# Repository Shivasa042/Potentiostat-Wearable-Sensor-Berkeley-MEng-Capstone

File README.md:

# Wearable Potentiostat — EIS Sweat Sensor (Berkeley MEng Capstone)

Portable Electrochemical Impedance Spectroscopy (EIS) system for real-time sweat analysis. Built around an **ESP32-S3** MCU and **Analog Devices AD5940/AD5941** analog front-end (AFE). Two electrodes on a watch back-plate contact skin; the system sweeps **1 Hz – 200 kHz** and reports complex impedance over **USB serial**, **BLE**, and **SD card**.

---

## Contents

1. [Hardware](#hardware)
2. [Repository structure](#repository-structure)
3. [Getting started](#getting-started)
4. [Usage](#usage) — serial commands, **Command Prompt / PowerShell**, Python scripts, scenarios
5. [Frequency range and sweep duration](#frequency-range-and-sweep-duration)
6. [How EIS works on this board](#how-eis-works-on-this-board)
7. [Errors, fixes, and known issues](#errors-fixes-and-known-issues)
8. [Firmware features](#firmware-features)
9. [Companion apps](#companion-apps) — **PHEW web app**, iOS, Android; BLE setup and usage
10. [Pin configuration](#pin-configuration)
11. [License](#license)

---

## Hardware

| Component | Details |
|-----------|---------|
| **MCU** | ESP32-S3 (240 MHz, Wi-Fi + BLE 5.0) |
| **AFE** | AD5940 / AD5941 — waveform generator, DFT engine, programmable-gain TIA |
| **Electrodes** | 2-electrode (CE0 + SE0), mounted on Apple Watch back-plate for sweat contact |
| **SPI bus** | Shared: AFE, SD card, and (Akshay PCB) ST7789 display — each device has its own CS |
| **Storage** | MicroSD card slot (FAT32, SPI) |
| **Wireless** | BLE — web companion, iOS app, or legacy Android |
| **Power** | USB-C or 3.7 V LiPo |
| **RCAL** | On-board calibration resistor, default **10 kΩ** — used internally by the AFE for ratiometric impedance calculation (not the load) |

### Two board variants

| | HELPStat V2 (bench/dev) | New_EIS_PCB_Akshay (final wearable) |
|---|---|---|
| AFE CS | GPIO 38 (or 11 on Eagle V2) | GPIO 38 |
| AFE interrupt | Hardware (GPIO 9) | None — SPI DFT polling |
| SD CS | GPIO 21 | GPIO 40 |
| Button | GPIO 7 | GPIO 13 |
| LED | GPIO 6 | None (use display) |
| Display | None | ST7789 240×280 SPI (ER-TFT1.69-4) — see [Pin configuration](#pin-configuration) |
| PSRAM | No | **Firmware uses internal RAM only** (`BOARD_HAS_PSRAM=0` in `eis-pcb-akshay`; avoids boot/USB instability when PSRAM does not init) |
| PlatformIO env | `lab-board-cs38` | `eis-pcb-akshay` |

KiCad 9 design files for the final PCB are in `boards/New_EIS_PCB_Akshay/`.

---

## Repository structure

```
src/main.cpp                   Firmware entry point, serial commands, measurement loop
src/eis_board_ui.cpp           SPI display driver for New_EIS_PCB_Akshay
lib/HELPStatLib/               Core library (AD5940 driver, EIS sweep, BLE, SD, LMA fit)
  HELPStat.cpp/h               High-level sweep, BLE transmit, SD save
  ad5940.c/h                   Low-level AD5940 register driver
  ad594x.cpp                   MCU-side SPI, interrupt/poll, resource init
  Impedance.c/h                Impedance math helpers
  lma.cpp/h                    Levenberg-Marquardt curve fitting (Rct, Rs)
  constants.h                  Pin definitions, board-specific macros
  eis_board_ui.h               Display UI header (C-linkage)
lib/Eigen/                     Eigen math library (used by LMA)
boards/custom_s3.json          PlatformIO board definition
boards/New_EIS_PCB_Akshay/     KiCad project (schematic + 4-layer PCB)
docs/                          Technical docs (features, modes, improvements)
testing/                       Python scripts for serial capture, plotting
web/helpstat-app/              PHEW web companion app (Chrome/Edge, Web Bluetooth)
ios/HELPStatCompanion/         Native iOS BLE companion (SwiftUI)
Originallibraries/             Legacy HELPStat reference (Android app, original firmware, Eagle PCB)
platformio.ini                 Build configuration
```

---

## Getting started

### Prerequisites

- **VS Code + PlatformIO** extension (builds the firmware)
- **Python 3.8+** with `pip install -r requirements.txt` (for testing scripts)
- **USB-C cable** to the board

### Build and flash

1. Open this folder in VS Code. PlatformIO auto-detects `platformio.ini`.
2. Connect the board via USB-C.
3. Build and upload (from project root):

```bash
# HELPStat V2 / bench board (CS=38, SPI DFT polling — no AFE IRQ required):
python -m platformio run -e lab-board-cs38 -t upload --upload-port COM3

# New EIS PCB (Akshay) — display + SD CS=40:
python -m platformio run -e eis-pcb-akshay -t upload --upload-port COM3
```

Replace `COM3` with your actual port. Close any serial monitor before uploading.

4. Open a serial monitor at **115200 baud**.

> **Windows:** After the first flash, you may need to unplug and re-plug USB once so the ESP32-S3 exits the ROM bootloader.

---

## Usage

All serial traffic is **115200 baud**, commands end with a **newline** (`\n` or `\r\n`).

### Command summary

| Command | Description |
|---------|-------------|
| `HELP` | List all commands |
| `STATUS` | Show wearable timer state and last sweep time |
| `SHOW` | Print current measurement parameters |
| `CHECK` | Read AD5940 chip ID (SPI connectivity test) |
| `MEASURE` | Run sweep with current parameters |
| `MEASURE:SAMPLE` | Default sweep: 200 kHz → 1 Hz, 10 pts/decade, 200 mV |
| `MEASURE:<14 params>` | Custom sweep (see below) |
| `SET:<14 params>` | Set parameters without measuring |
| `WEARABLE:ON` / `OFF` | Enable/disable automatic timed sweeps |
| `INTERVAL:N` | Auto-sweep interval in seconds (min 10, default 300) |
| `STOP` | Abort a running sweep immediately (also works mid-sweep) |
| `RCAL:ohms` | Set RCAL value and save to NVS (e.g. `RCAL:10000`) |
| `RCAL:SHOW` | Print stored and runtime RCAL values |
| `DISPLAYRANGE:min,max,val[,title]` | Update SPI display (Akshay PCB only) |

### 14-parameter `MEASURE` format

```
MEASURE:mode,startFreq,endFreq,numPoints,biasVolt,zeroVolt,rcalVal,extGain,dacGain,rct_est,rs_est,numCycles,delaySecs,amplitude
```

| # | Parameter | Example | Notes |
|---|-----------|---------|-------|
| 1 | mode | 0 | 0=EIS, 1=CV, 2=IT, 3=CP, 4=DPV, 5=SWV, 6=OCP |
| 2 | startFreq | 200000 | Hz (often the high end of the sweep) |
| 3 | endFreq | 1 | Hz (often the low end) |
| 4 | numPoints | 10 | Points per decade (log sweep) |
| 5 | biasVolt | 0.0 | DC bias (V) |
| 6 | zeroVolt | 0.0 | Zero voltage (V) |
| 7 | rcalVal | 10000 | Calibration resistor (Ohms) — match your board's RCAL |
| 8 | extGain | 1 | Excitation buffer gain (1=x2) |
| 9 | dacGain | 1 | DAC gain (1=x1) |
| 10 | rct_est | 127000 | Estimated Rct (Ohms) — seed for LMA fit |
| 11 | rs_est | 150 | Estimated Rs (Ohms) — seed for LMA fit |
| 12 | numCycles | 0 | Repeat cycles |
| 13 | delaySecs | 0 | Delay between cycles (s) |
| 14 | amplitude | 200 | AC excitation (mV, 0-800) |

**Example — full-span sweep (200 kHz → 1 Hz, 5 pts/decade, 10 kΩ RCAL, 150 mV):**

```
MEASURE:0,200000,1,5,0.0,0.0,10000.0,1,1,127000.0,150.0,0,0,150
```

### Running an EIS sweep from Command Prompt or PowerShell (Windows)

Windows does not include a serial terminal in `cmd.exe`. Use **Python + pyserial** (same as the repo's test scripts).

1. **Install once:**

```bash
pip install pyserial
```

2. **Close anything else using the COM port** (VS Code Serial Monitor, another Python script, etc.).

3. **Send a command and print the response** — adjust `COM3` and timeouts as needed. Long sweeps can take **many minutes**; increase the inner `while` time limit if needed.

**Default firmware sample sweep (`MEASURE:SAMPLE`):**

```powershell
python -c "import serial,time; s=serial.Serial('COM3',115200,timeout=600); s.write(b'MEASURE:SAMPLE\r\n'); t=time.time();
while time.time()-t<900:
    line=s.readline()
    if line: print(line.decode(errors='replace').rstrip())"
```

**Custom 14-parameter sweep** (same example as the table above):

```powershell
python -c "import serial,time; s=serial.Serial('COM3',115200,timeout=600); s.write(b'MEASURE:0,200000,1,5,0.0,0.0,10000.0,1,1,127000.0,150.0,0,0,150\r\n'); t=time.time();
while time.time()-t<900:
    line=s.readline()
    if line: print(line.decode(errors='replace').rstrip())"
```

4. **Interactive alternative** — type commands by hand:

```bash
python -m platformio device monitor -p COM3 -b 115200
```

Then type `MEASURE:SAMPLE` or a full `MEASURE:0,...` line and press Enter.

### Python scripts in `testing/`

```bash
# Default 2-point sweep (10 kHz → 1 kHz):
python testing/scenario1_serial_sample.py COM3

# Single frequency at 10 kHz:
python testing/scenario1_serial_sample.py COM3 10000
```

### Three usage scenarios

1. **Laptop + USB (development)** — Flash, open serial (or Command Prompt as above), send `MEASURE:SAMPLE`, read CSV from the terminal or a script.
2. **Standalone (button + SD)** — Press button on GPIO 7 (bench) or GPIO 13 (Akshay). Results save to SD at `/eis/sweep_1Hz_200kHz.csv` (path/name set in firmware).
3. **Wearable (BLE, battery)** — Send `WEARABLE:ON` once. Board auto-sweeps at the configured interval. Data via BLE (web/iOS) and SD card.

---

## Frequency range and sweep duration

- **Practical sweep span in this firmware:** about **1 Hz – 200 kHz** (high end is what the code and gain schedule target; AD5941 family supports a similar band depending on clock and configuration).
- **Number of frequency points** (log sweep, `startFreq > endFreq`):

  `SweepPoints = (1.5 + (log10(startFreq) - log10(endFreq)) x numPoints) - 1`

  Example: 200 kHz → 1 Hz at **5 points/decade** = **27 points**; at **10 points/decade** = **54 points**.

- **Time per point** depends on frequency (settling + DFT). **Low Hz is slow** (several seconds per point is normal).

### Measured sweep timings (10 kOhm load resistor)

| Sweep | Points | Approx. duration | Notes |
|-------|--------|-------------------|-------|
| Single-point 200 kHz | 1 | ~2 s | Fastest; use small span trick (see below) |
| Single-point 200 Hz | 1 | ~3 s | |
| 200 kHz → 10 Hz, 5 pts/decade | 22 | ~30 s | Good for quick characterization |
| 200 kHz → 1 Hz, 5 pts/decade | 27 | **~108 s** | Full wearable range (`MEASURE:SAMPLE` default) |
| 200 kHz → 1 Hz, 10 pts/decade | 54 | ~4-6 min | High-resolution; pass `numPoints=10` in custom `MEASURE:` |

Low-frequency points (< 10 Hz) are dominated by DFT collection time inside the AD5940 — this is a hardware constraint. The 1 Hz point alone takes several seconds.

### Sweep speed tuning (firmware defaults)

The firmware balances speed and accuracy through these parameters:

| Parameter | Value | Location | Effect |
|-----------|-------|----------|--------|
| Settling periods | 2 cycles | `HELPStat.cpp settlingDelay()` | Fewer AC cycles before DFT capture |
| Averages per point | 1 | `HELPStat.h _numAverages` | Single validated measurement per frequency |
| Gain-switch delay | 50 ms | `HELPStat.cpp` / `runSweep()` | Reduced from 200 ms; stable with resistive loads |
| Default pts/decade | 5 | `main.cpp MEASURE:SAMPLE` | 27 points for full 1 Hz–200 kHz span |

These can be increased for noisier electrochemical loads (e.g., set `_numAverages = 3` for sweat sensors). The custom `MEASURE:` command accepts any `numPoints` value.

### Sample measurement results (10 kOhm load resistor across CE0-SE0)

| Test | Magnitude | Phase | Rct (fit) | Rs (fit) |
|------|-----------|-------|-----------|----------|
| 200 kHz single | ~335 Ohm | ~2.6 deg | — | — |
| 200 Hz single | ~332 Ohm | ~0.05 deg | — | — |
| 200 kHz → 10 Hz (22 pts) | 311-357 Ohm | -4 to +4 deg | 32.3 Ohm | 323.4 Ohm |
| 200 kHz → 1 Hz (27 pts) | 303-365 Ohm | -3.4 to +4.5 deg | -29.5 Ohm | 325.5 Ohm |

These values are from a bench test with a nominal 10 kOhm resistor (actual ~327 Ohm measured — the parallel combination of the 10 kOhm load with the AFE's internal RTIA/feedback path produces the observed lower magnitude).

### Single-frequency caveat

If **`startFreq` equals `endFreq`**, the sweep math yields **zero points** and the measurement hangs. For an effectively single frequency, use a **tiny span**, e.g. `200000` → `199000` with `numPoints=1`.

### Stopping a sweep mid-flight

You can abort a running sweep at any time. The firmware checks for abort requests between each frequency point.

| Method | How | Where |
|--------|-----|-------|
| **PHEW web app** | Click the red **Stop** button (replaces "Run sweep" during a sweep) | `web/helpstat-app/` |
| **Serial** | Send `STOP` (case-insensitive) over the serial connection | Any serial terminal, pyserial script |
| **BLE programmatic** | Write byte `2` to the `start` characteristic | Any BLE client using the GATT UUIDs |

On abort the firmware shuts down the AFE cleanly, prints any partial CSV data collected so far, and skips the Rct/Rs curve fit and BLE data transmission (partial data would produce unreliable fits). The board is immediately ready for the next command.

### Long sweeps + USB

On some PCs the ESP32-S3 **USB Serial/JTAG** link can **glitch or disconnect** during long runs. The firmware still **writes results to the SD card** when a card is present — check `/eis/` on the card if the serial stream stops early.

---

## How EIS works on this board

1. AD5940 waveform generator outputs a sine wave at the target frequency through **CE0** (counter electrode).
2. Current flows through the **load** (sweat between the two electrodes) and returns through **SE0** (sense electrode).
3. The **HSTIA** (transimpedance amplifier) converts the current to voltage. Gain resistor is auto-selected per frequency band.
4. The on-chip **DFT engine** extracts real and imaginary components.
5. Impedance is computed ratiometrically against **RCAL** (the known calibration resistor on the board).
6. The firmware sweeps all frequencies, outputting CSV with columns: `Frequency(Hz), Real(Ohm), Imaginary(Ohm), Magnitude(Ohm), Phase(Degrees)`.
7. A Levenberg-Marquardt fit estimates **Rct** (charge transfer resistance) and **Rs** (solution resistance).

### RCAL vs load — what each does

- **RCAL** (on-board, 10 kΩ default): An internal **reference** resistor. The AFE measures it at each frequency to calibrate its gain path. It is **not** the unknown under test. You do not wire CE0/SE0 to RCAL for normal EIS.
- **Load** (between CE0 and SE0): The **unknown impedance** you are measuring. For bench testing this is often a known resistor. For the wearable, this is **sweat/skin** between the watch electrodes.

If there is **no conductive path** between CE0 and SE0 (open circuit, dry skin, electrodes not touching), the DFT engine gets no valid signal and times out — producing `NaN` results.

---

## Errors, fixes, and known issues

### DFT poll timeout → NaN results

**Symptom:** `ERROR: DFT poll timeout (~30 s)` and CSV values are `nan`.

| Cause | Fix |
|-------|-----|
| **No load between CE0 and SE0** | Bench: place a **known resistor** across CE0-SE0. Wearable: moist contact / sweat path. |
| **Dry skin / no sweat** | Electrodes need a conductive medium; saline drop for testing if needed. |
| **Wrong AFE CS pin** | Match `CS` in `constants.h` to your PCB (38 for Akshay / this bench setup; 11 for HELPStat V2 Eagle). |
| **Missing interrupt wire** (HELPStat V2 only) | AFE GPIO0 → MCU GPIO9. Akshay PCB uses **SPI polling** instead (`AFE_USE_HARDWARE_IRQ_GPIO=0` in `lab-board-cs38` / Akshay path). |

### PSRAM / boot loop / USB drops right after boot (Akshay env)

**Symptom:** ROM prints `PSRAM ID read error` or serial **disconnects** mid-banner; `ClearCommError` / port errors in Python.

**Fix:** Build **`eis-pcb-akshay`** with **PSRAM disabled** in `platformio.ini` (`board_build.psram_type = disabled`, `-DBOARD_HAS_PSRAM=0`). The chip may report embedded PSRAM in esptool while the ROM/app init still fails; **internal RAM** is enough for this firmware.

### Display not showing anything (Akshay PCB — ST7789)

**Symptom:** Firmware prints `eis_board_ui: display ready (ST7789)` but the screen is dark.

| Cause | Fix |
|-------|-----|
| **Backlight not enabled** | GPIO 14 (ESP.PWM) drives Q3 N-FET gate to sink LED cathode. Firmware now drives GPIO 14 HIGH after display init. |
| **FPC cable not seated** | The 18-pin 0.5 mm FPC connector (J13) has a flip-top ZIF latch. Ensure the cable is fully inserted and the latch is **closed**. |
| **SPI bus contention** | Firmware deselects AD5941 (GPIO 38 HIGH) before display transactions. If issues persist, check solder joints on J13. |

**Display backlight circuit (from KiCad):**

```
+3V3 → R (0402 current limiter) → J13 pin 3 (LED anode)
J13 pin 2 (LED cathode, /K) → Q3 drain (IRLML6344 N-FET)
Q3 source → GND
Q3 gate ← GPIO 14 (ESP.PWM)
```

The display is a **ER-TFT1.69-4** (BuyDisplay), 1.69" 240x280 IPS TFT, ST7789V controller, 4-wire SPI. Datasheet: [ER-TFT1.69-4](https://www.buydisplay.com/download/manual/ER-TFT1.69-4_Datasheet.pdf), [ST7789V IC](https://www.buydisplay.com/download/ic/ST7789.pdf).

On boot, the firmware runs a diagnostic sequence: **3 backlight blinks** (GPIO 14 toggle), then fills **RED → GREEN → BLUE** (600 ms each), then displays **HELLO WORLD** in white text. If no blinks are visible, the issue is hardware (FPC cable, backlight circuit, or display module).

### COM port issues (Windows)

| Symptom | Fix |
|---------|-----|
| `PermissionError` / port busy | Another program holds the port. Close Serial Monitor and kill stuck Python processes. |
| Port disappears after flash | Unplug and re-plug USB once (common on ESP32-S3). |
| Upload fails | Close serial monitor before uploading. |

### Build errors

| Error | Fix |
|-------|-----|
| `pio not recognized` | Use `python -m platformio run ...` |
| `#define CS` clash with Adafruit | Do not include `constants.h` before Adafruit headers in display code — already handled in `eis_board_ui.cpp`. |
| `-DMOSI` / `-DMISO` / `-DSCK` build flags | Do **not** pass these on Arduino-ESP32 3.x — they clash with `pins_arduino.h`. Edit `constants.h` instead. |

### EIS data quality

| Issue | Explanation |
|-------|-------------|
| `inf` magnitude | Open circuit or loose electrode connection. |
| Jumps at certain frequencies | RTIA gain switching; hysteresis helps but extreme mismatches can still show artifacts. |
| Fit Rct/Rs stuck at defaults | Poor data; fix wiring and **RCAL** first, then tune `rct_est` / `rs_est`. |
| Slow sweep at low frequencies | Normal — more cycles at low Hz. |

---

## Firmware features

- **Data validation**: Bad DFT measurements (NaN, inf, out-of-range) are detected and retried (up to 4x) or recorded as NaN.
- **DFT poll timeout**: ~30 s timeout prevents infinite hangs on open circuit or stuck interrupt path.
- **Gain hysteresis**: 10% frequency margin on RTIA switching reduces oscillation at band boundaries.
- **Averaging**: Configurable per-point averaging (`_numAverages`, default 1; increase for noisy electrochemical loads).
- **Speed-optimized defaults**: Settling delay (2 AC periods), 50 ms gain-switch delays, 5 pts/decade — full 1 Hz–200 kHz sweep in ~108 s.
- **Sweep abort**: `STOP` serial command or BLE `start=2` write aborts a running sweep between frequency points. AFE shuts down cleanly; partial data is printed.
- **SPI DFT polling**: On PCBs without AFE→MCU interrupt (Akshay), DFTRDY is polled over SPI.
- **RCAL in NVS**: `RCAL:` stores calibration value in flash (survives reboot).
- **Wearable auto-sweep**: Timer-based sweeps for field use (`WEARABLE:ON`, `INTERVAL:N`).
- **Display UI** (Akshay): Live sweep progress on ST7789; `DISPLAYRANGE` serial command for custom display.
- **Display backlight** (Akshay): GPIO 14 PWM drives Q3 N-FET for backlight control; blink test on boot.
- **Temperature logging**: AD5940 die temperature readout (approximate).

See `docs/NEW_FEATURES.md` for more detail.

---

## Companion apps

**GitHub only stores source code.** Nothing is automatically "built" or hosted for you. You run each app locally (or deploy the web app to your own hosting). The firmware must be on the board and **BLE enabled** in the sketch for phone/browser connections to work.

| Platform | Location | Notes |
|----------|----------|-------|
| **PHEW Web App** (Chrome/Edge) | `web/helpstat-app/` | Static site + Web Bluetooth. Needs **HTTPS or localhost**. |
| **iOS** (native) | `ios/HELPStatCompanion/` | Open in **Xcode**, build to a **physical iPhone** (recommended) or Simulator (BLE is limited). |
| **Android** (legacy) | `Originallibraries/HELPStat-main 4/HELPStat/Software/App/` | Open in **Android Studio**, Gradle build. Not actively maintained. |

### Bluetooth: advertised name, pairing, and which devices can connect

- **Name you should see when scanning:** **`HELPStat`**. The firmware sets this in `BLEDevice::init("HELPStat")` in `lib/HELPStatLib/HELPStat.cpp`. The PHEW web app and iOS companion filter on that name (`web/helpstat-app/js/constants.js`, `ios/.../GattConstants.swift`). Some OS Bluetooth lists show only a generic "LE" device if the name packet is delayed; the companion apps still discover **`HELPStat`** once advertising is up.

- **Not like a Bluetooth speaker.** The board exposes **Bluetooth Low Energy (BLE)** with a **custom GATT service** (primary service UUID **`4fafc201-1fb5-459e-8fcc-c5c9c331914b`**, defined with characteristics in `lib/HELPStatLib/HELPStat.h`). There is no standard "pair and any app works" profile for EIS data.

- **Who can connect:** Any **phone, tablet, or PC** that runs **client software** implementing that GATT layout — this repo's **PHEW web app** (Chrome/Edge + Web Bluetooth), **iOS HELPStatCompanion**, or **legacy Android** app — or **your own** app using the same UUIDs. Generic system "Pair new device" flows are not sufficient by themselves.

- **Firmware:** `setup()` must call **`BLE_setup()`** (already the case in `src/main.cpp`). Without running firmware, nothing advertises as **`HELPStat`**.

### PHEW Web App (`web/helpstat-app/`)

**PHEW** (Portable Health & Electrochemical Wearable) is the browser-based companion for this potentiostat. It connects to the board over **Bluetooth Low Energy**, lets you configure and trigger EIS sweeps, and visualizes results with interactive charts — all from a single static webpage with no server or installation required beyond a local file server.

#### What the app does

| Tab | Function |
|-----|----------|
| **Live** | Connect to the board via BLE, optionally adjust sweep parameters, and click **Run sweep** to trigger an EIS measurement. Incoming data streams in real-time over BLE notifications. When the sweep completes (the firmware sends back Rct and Rs fit values), it is automatically saved and the view switches to History. |
| **History** | Browse all saved sweeps organized by **Pacific calendar day** (America/Los_Angeles timezone). Select a day and sweep to view **Nyquist** (Zreal vs Zimag), **Bode magnitude** (|Z| vs log frequency), and **Bode phase** (phase vs log frequency) plots rendered with Chart.js. **Export JSON** downloads the whole day; **Export CSV** downloads the **selected sweep** as spreadsheet-friendly columns (same layout as serial CSV). Import JSON from another device. |
| **About** | Platform compatibility notes and links back to this README. |

#### Data flow

```
Board (firmware)  ──BLE GATT notifications──►  PHEW (browser)
                                                  │
                            frequency, real, imag, phase, magnitude
                            arrive point-by-point; Rct/Rs arrive last
                                                  │
                                                  ▼
                                          IndexedDB (browser)
                                          grouped by Pacific day
                                                  │
                                        ┌─────────┴─────────┐
                                        ▼                   ▼
                                   Chart.js plots     Export JSON / CSV
```

All data is stored **locally in your browser** (IndexedDB). Nothing is sent to any server. Clearing browser data removes saved sweeps — use **Export JSON** (full day backup) or **Export CSV** (single sweep for Excel, Python, or comparison with firmware serial logs) to keep copies offline.

#### Default sweep parameters (match firmware)

The form pre-fills values that match the firmware's `MEASURE:SAMPLE` defaults:

| Parameter | Default value | Notes |
|-----------|---------------|-------|
| Rct estimate | 127,000 Ω | Seed for Levenberg-Marquardt fit |
| Rs estimate | 150 Ω | Seed for LMA fit |
| Start frequency | 200,000 Hz | High end of sweep |
| End frequency | 1 Hz | Low end of sweep |
| Points / decade | 5 | 27 total points for full span |
| Rcal | 10,000 Ω | Must match on-board calibration resistor |
| Amplitude | 200 mV | AC excitation (set in firmware, not in web form) |

You can override any field before clicking **Run sweep**. Leave a field blank to use the firmware's built-in default.

#### How to access the PHEW web app (step by step)

1. **Why not double-click `index.html`?**
   [Web Bluetooth](https://developer.mozilla.org/en-US/docs/Web/API/Web_Bluetooth_API) requires a **secure context** — the browser must see **`https://`** or **`http://localhost`** (or `127.0.0.1`). Opening the file directly as `file://` blocks Bluetooth access.

2. **Start a local web server (one instance only).** Open a terminal, go to the app folder, and serve it on a free port (default **8080**):

   **macOS / Linux / Windows Command Prompt:**

   ```bash
   cd web/helpstat-app
   python -m http.server 8080
   ```

   **Windows PowerShell (built-in 5.x):** The `&&` chain operator is **not** available in older PowerShell. Use **two lines**, or a **semicolon**:

   ```powershell
   Set-Location web\helpstat-app
   python -m http.server 8080
   ```

   ```powershell
   Set-Location web\helpstat-app; python -m http.server 8080
   ```

   (Run these from the **repository root**, or use the full path to `web\helpstat-app`. **PowerShell 7+** supports `&&` like bash.)

   Keep this terminal **open** while you use the app. You should see a line such as `Serving HTTP on 0.0.0.0 port 8080`.

   **Python:** If `python` is not found, try `py -m http.server 8080` (Windows launcher) or `python3`. Install Python 3.8+ from [python.org](https://python.org) if needed.

   **Port already in use:** If 8080 is taken, pick another port (example **8765**):

   ```bash
   python -m http.server 8765
   ```

   Then open `http://localhost:8765` instead. **Do not** start multiple `http.server` processes on the **same** port — you can get failed loads or empty responses; close duplicate terminals or choose a new port.

3. **Open the app in Chrome or Edge** — go to: [http://localhost:8080](http://localhost:8080) (or your chosen port).

   You should see the **PHEW** header with **Live** / **History** / **About** tabs.

4. **Prepare the hardware.** Power the board (**USB-C** or battery). Firmware must be running so **BLE advertises** as **`HELPStat`** (`BLE_setup()` in `setup()` — already in this repo’s `src/main.cpp`). For a **USB serial** session at the same time, use another tool (e.g. PlatformIO monitor) and avoid port conflicts; BLE and USB can often be used together depending on your setup.

5. **Connect from the Live tab:**
   - Click **Connect**.
   - When the browser asks for Bluetooth permission, choose **`HELPStat`** and confirm pairing/connection.
   - The status line should show that you are connected (e.g. connected to **HELPStat**).

6. **Run a sweep:**
   - (Optional) Expand **Sweep parameters** and edit fields, or leave defaults to match firmware `MEASURE:SAMPLE`-style behavior.
   - Click **Run sweep**. A progress area shows point count, current frequency, and elapsed time.
   - To **abort**, click **Stop** (replaces **Run sweep** while a run is active). The firmware stops cleanly; partial data are not treated as a completed sweep.
   - Wait for completion. Approximate times depend on span and points/decade (e.g. **~108 s** for a full **200 kHz → 1 Hz** span at **5** pts/decade — see [Frequency range and sweep duration](#frequency-range-and-sweep-duration)).
   - When the sweep finishes, the app **saves** the run and typically moves to **History** with plots.

7. **History — review, import, export:**
   - **Day** and **Sweep** dropdowns: pick a calendar day (Pacific time) and a sweep within that day.
   - Charts: **Nyquist**, **Bode magnitude**, **Bode phase**.
   - **Export JSON:** downloads that **entire day** as `phew_YYYY-MM-DD.json` (all sweeps in one file). Good for backup or moving data to another PC.
   - **Export CSV:** downloads **only the selected sweep** as `phew_YYYY-MM-DD_sweepN.csv` — columns match serial CSV style: `Frequency(Hz),Real(Ohm),Imaginary(Ohm),Magnitude(Ohm),Phase(Degrees)`, plus footer lines for **Rct** / **Rs** when available.
   - **Import:** load a JSON file from another session or machine to view in History.

8. **Stop the server** when done: in the terminal where `http.server` is running, press **Ctrl+C**.

#### PHEW troubleshooting

| Symptom | What to try |
|--------|-------------|
| Browser says Bluetooth is blocked or unavailable | Use **Chrome** or **Edge** on a supported OS; the page must be **`http://localhost/...`** or **HTTPS**, not `file://`. |
| **Connect** never finds a device | Board powered? Firmware flashed? On Windows, Bluetooth **on**? Unpair old **HELPStat** entries in system Bluetooth settings if stuck. |
| Page does not load / connection reset | Ensure **exactly one** HTTP server is bound to that port; try another port or close duplicate `python -m http.server` windows. |
| PowerShell errors on `cd ... && python ...` | Use **semicolon** or **two lines** (see step 2), or upgrade to **PowerShell 7+**. |
| iPhone / iPad | **Web Bluetooth is not supported** on iOS Safari. Use the **iOS** app (`ios/HELPStatCompanion/`) or import JSON from a desktop session. |

#### Supported browsers and platforms

| Platform | Browser | BLE support |
|----------|---------|-------------|
| **Windows** | Chrome, Edge | Full (recommended) |
| **macOS** | Chrome, Edge | Full |
| **Linux** | Chrome | Full (may need `chrome://flags/#enable-web-bluetooth`) |
| **Android** | Chrome | Full |
| **iPhone / iPad** | Safari, Chrome | **No** — Apple does not expose Web Bluetooth. Use the native iOS app below, or use the History tab to import JSON from another device. |

#### PWA / home screen install

PHEW includes a `manifest.webmanifest` so browsers offer **"Add to Home Screen"** / **"Install App"**. This creates a standalone shortcut that opens full-screen. Offline use is limited to viewing previously saved data; BLE requires a network context.

### iOS app (`ios/HELPStatCompanion/`)

1. You need a **Mac** with **Xcode** (15+ as noted in the table; use a current Xcode that supports the project format).

2. Open **`ios/HELPStatCompanion/HELPStatCompanion.xcodeproj`** in Xcode.

3. Select a run destination:
   - **Physical iPhone** (USB or wireless debugging): best for real BLE to the wearable.
   - **Simulator**: CoreBluetooth behavior is limited; prefer a real device for end-to-end tests.

4. Press **Run**. The first time, you may need to set your **Team** under Signing & Capabilities so Xcode can sign the app.

5. Apple does **not** install apps from GitHub automatically; **TestFlight** or the **App Store** only happen if you create an Apple Developer distribution pipeline yourself.

### Android app (legacy)

1. Install **Android Studio** (current stable).

2. **Open** the Gradle project at
   `Originallibraries/HELPStat-main 4/HELPStat/Software/App/`
   (the folder that contains the root `build.gradle.kts`).

3. Let Gradle sync, connect a phone with **USB debugging**, or use an emulator (BLE on emulators is often unavailable or flaky).

4. **Run** the app module from Android Studio.

5. This tree is **legacy**; expect older SDK assumptions and possible migration work.

---

## Pin configuration

### HELPStat V2 / bench board

| Signal | GPIO | Notes |
|--------|------|-------|
| MOSI | 35 | SPI data out |
| MISO | 37 | SPI data in |
| SCK | 36 | SPI clock |
| CS (AFE) | 38 | AD5940 chip select (11 on V2 Eagle) |
| RESET | 10 | AD5940 reset |
| INTERRUPT | 9 | AD5940 GPIO0 → MCU |
| CS_SD | 21 | SD card chip select |
| BUTTON | 7 | Push-button (active LOW) |
| LED | 6 | Status LED |

### New_EIS_PCB_Akshay — MCU, SD, AFE

| Signal | GPIO | Notes |
|--------|------|-------|
| MOSI | 35 | Shared SPI |
| MISO | 37 | Shared SPI |
| SCK | 36 | Shared SPI |
| CS (AFE) | 38 | AD5940 chip select |
| RESET | 10 | AD5940 reset |
| CS_SD | 40 | SD card chip select |
| BUTTON | 13 | SW1 push-button |

### New_EIS_PCB_Akshay — display (ST7789, ER-TFT1.69-4)

The display shares the **same SPI bus** (SCK, MOSI, MISO) as the AFE and SD; only **CS / DC / RST / BL** are display-specific.

| Display signal | GPIO | KiCad net | J13 FPC pin | Notes |
|----------------|------|-----------|-------------|-------|
| **TFT CS** | 39 | /CS.SCREEN | 8 | Display chip select |
| **TFT DC** | 3 | /DC | 7 | Data / command |
| **TFT RST** | 21 | /SCREEN.RST | 11 | Display hardware reset |
| **TFT BL** | 14 | /ESP.PWM | — (via Q3) | Backlight control — drives Q3 N-FET gate |
| **SCK** | 36 | /SCLK | 9 | Shared with AFE / SD |
| **MOSI** | 35 | /MOSI | 10 | Shared |
| **MISO** | 37 | /MISO | — | Shared (not used by display) |

**J13 FPC connector full pinout (18-pin, 0.5 mm pitch ZIF):**

| Pin | Net | Function |
|-----|-----|----------|
| 1 | GND | Ground |
| 2 | /K | LED cathode → Q3 drain (backlight) |
| 3 | +3V3 (via R) | LED anode (backlight, current-limited) |
| 4 | +3V3 | Display power |
| 5 | GND | Ground |
| 6 | GND | Ground |
| 7 | /DC | Data/Command (GPIO 3) |
| 8 | /CS.SCREEN | Chip select (GPIO 39) |
| 9 | /SCLK | SPI clock (GPIO 36) |
| 10 | /MOSI | SPI data (GPIO 35) |
| 11 | /SCREEN.RST | Reset (GPIO 21) |
| 12 | GND | Ground |
| 13 | /CTP_SCL | Touch I2C clock (capacitive touch, optional) |
| 14 | /CTP_SDA | Touch I2C data (capacitive touch, optional) |
| 15 | /CTP_RST | Touch reset (GPIO 47) |
| 16 | /CTP_INT | Touch interrupt (GPIO 48) |
| 17 | +3V3 | Touch power |
| 18 | GND | Ground |

Panel: **240x280** IPS TFT, ST7789V controller, 4-wire SPI (see `src/eis_board_ui.cpp`).

No dedicated AFE interrupt line; firmware uses SPI polling for DFT ready.

---

## License

MIT License — Copyright (c) 2024 Linnes Lab, Purdue University

See LICENSE file for full text.

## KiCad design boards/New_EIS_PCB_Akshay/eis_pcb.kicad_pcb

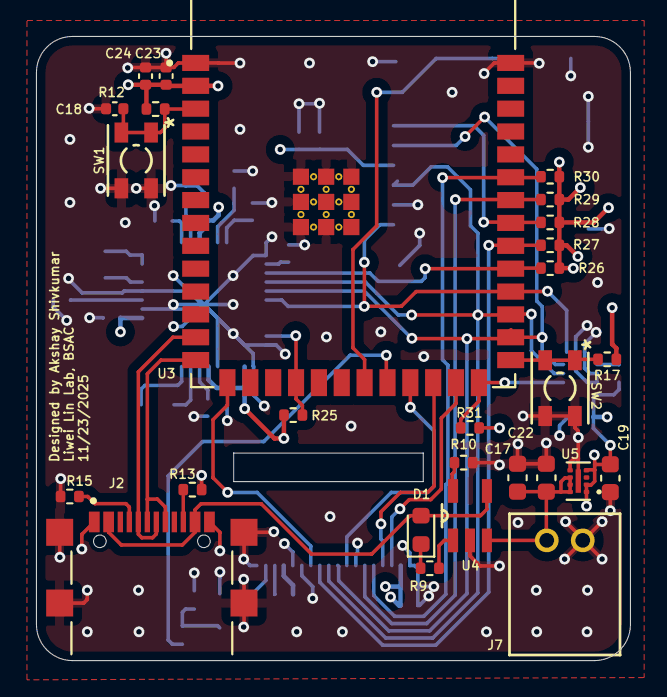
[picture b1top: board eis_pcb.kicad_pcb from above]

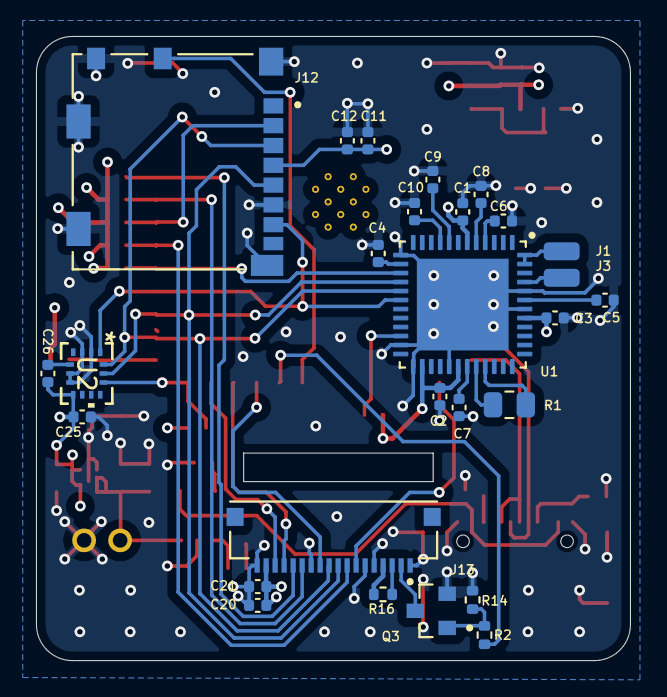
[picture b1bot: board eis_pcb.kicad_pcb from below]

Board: 4 copper layers, 33.0 x 34.7 mm, 54 parts (27 on the bottom side), 43 nets.

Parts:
C1, C2, C3, C9, C10: 100n; C_0402_1005Metric
C4, C6, C7, C8: 470n; C_0402_1005Metric
C5: 4.7u; C_0402_1005Metric
C11, C18: 10uF; C_0402_1005Metric
C12, C25, C26: 100nF; C_0402_1005Metric
C17: 10uF; C_0603_1608Metric
C19, C22: 1uF; C_0603_1608Metric
C20: 4.7uF; C_0402_1005Metric
C21: 0.1uF; C_0402_1005Metric
C23, C24: 1uF; C_0402_1005Metric
D1: LED; LED_0603_1608Metric
J1, J3: Conn_01x01_Socket; SolderWirePad_1x01_SMD_1x2mm
J2: GSB1C41110SSHR; AMPHENOL_GSB1C41110SSHR
J7: Conn_01x02_Socket; CONN_S2B-PH-K-S_JST
J12: 104031-0811; MOLEX_104031-0811
J13: 10051922-1810ELF; AMPHENOL_10051922-1810ELF
Q3: IRLML6344TRPBF; TRANS_IRLML6344TRPBF
R1: 10k; R_0805_2012Metric
R2: 100R; R_0402_1005Metric
R9, R10, R26, R27, R28, R29, R30, R31: 4.7k; R_0402_1005Metric
R12, R17, R25: 10k; R_0402_1005Metric
R13, R15: 5.1k; R_0402_1005Metric
R14: 100k; R_0402_1005Metric
R16: 10R; R_0402_1005Metric
SW1, SW2: SW_Push_Dual; SWITCH_0SMTRLFS-L
U1: AD5941BCPZ; QFN50P700X700X80-49N
U2: LGA14-L_2P59X3P1X0P5_STM; LGA14-L_2P59X3P1X0P5_STM-L
U3: ESP32-S3-WROOM-1-N8R8; XCVR_ESP32S3WROOM1N8R8
U4: MCP73831T-2DCI_OT; SOT95P270X145-5N
U5: NCP186AMX330TAG; PSON40P160X120X45-9N

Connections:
+3V3: C1.1, C2.1, C3.1, C11.1, C12.1, C19.1, C20.1, C21.1, C23.1, C24.1, C25.1, C26.1, J12.4 (VDD), J13.4, J13.17, R12.1, R16.1, R17.1, R25.2, R26.2, R27.2, R28.2, R29.2, R30.2, R31.2, U1.6 (DVDD), U1.26 (IOVDD), U1.30 (AVDD), U1.41 (AVDD), U3.2 (3V3), U5.1 (OUT), U5.2 (OUT__1), U5.4 (FB/ADJ)
+5V: D1.2 (A), J2.A4_B9 (VBUS_A), J2.B4_A9 (VBUS_B), U4.4 (VDD)
+BATT: C17.1, C22.1, J7.1, U4.3 (VBAT), U5.6 (EN), U5.7 (IN), U5.8 (IN__1)
/AFE.RST: R25.1, U1.22 (~RESET), U3.18 (IO10)
/AVDD.REG: C8.1, U1.5 (AVDD_REG)
/BIAS.0: C9.1, U1.8 (VBIAS0)
/BIAS.CAP: C7.1, U1.31 (VBIAS_CAP)
/BOOT: R17.2, SW2.1, SW2.2, U3.27 (IO0)
/CS.AFE: R26.1, U1.15 (~CS), U3.31 (IO38)
/CS.IMU: R31.1, U3.26 (IO45)
/CS.SCREEN: J13.8, R27.1, U3.32 (IO39)
/CS.SD: J12.2 (CD/DAT3), R28.1, U3.33 (IO40)
/CTP_INT: J13.16, U3.25 (IO48)
/CTP_RST: J13.15, U3.24 (IO47)
/CTP_SCL: J13.13, R29.1, U3.34 (IO41)
/CTP_SDA: J13.14, R30.1, U3.35 (IO42)
/DATA+: J2.A6 (DP1), J2.B6 (DP2), U3.14 (IO20)
/DATA-: J2.A7 (DN1), J2.B7 (DN2), U3.13 (IO19)
/DC: J13.7, U3.15 (IO3)
/DVDD.1V8: C4.1, U1.14 (DVDD_REG_1V8)
/ESP.PWM: R2.1, U3.22 (IO14)
/K: J13.2, Q3.3
/MCU.RST: C18.1, R12.2, SW1.1, SW1.2, U3.3 (EN)
/MISO: J12.7 (DAT0), U1.18 (MISO), U3.30 (IO37)
/MOSI: J12.3 (CMD), J13.10, U1.17 (MOSI), U3.28 (IO35)
/RE: J1.1, U1.47 (CE0), U1.48 (RE0)
/REF.1V8: C5.1, U1.43 (VREF_1V8)
/REF.2V5: C6.1, U1.4 (VREF_2V5)
/SCLK: J12.5 (CLK), J13.9, U1.16 (SCLK), U3.29 (IO36)
/SCREEN.RST: J13.11, U3.23 (IO21)
/SW1: J12.9 (SW-1), U3.21 (IO13)
/WE: J3.1, U1.45 (SE0)
/ZERO.0: C10.1, U1.9 (VZERO0)
GND: C1.2, C2.2, C3.2, C4.2, C5.2, C6.2, C7.2, C8.2, C9.2, C10.2, C11.2, C12.2, C17.2, C18.2, C19.2, C20.2, C21.2, C22.2, C23.2, C24.2, C25.2, J2.A1_B12 (GND_A), J2.B1_A12 (GND_B), J2.SH1 (SHIELD), J2.SH2 (SHIELD__1), J2.SH3 (SHIELD__2), J2.SH4 (SHIELD__3), J7.2, J12.6 (VSS), J12.10 (SW-2), J12.G1 (GND), J12.G2 (GND), J12.G3 (GND), J12.G4 (GND), J13.1, J13.5, J13.6, J13.12, J13.18, Q3.2, R10.1, R13.2, R14.2, R15.2, SW1.3, SW1.4, SW2.3, SW2.4, U1.13 (DGND), U1.23 (DGND), U1.25 (DGND), U1.29 (AGND), U1.42 (AGND), U1.44 (AGND_REF), U1.49 (EXP), U3.1 (GND), U3.40 (GND), U3.41_1 (GND), U3.41_2 (GND), U3.41_3 (GND), U3.41_4 (GND), U3.41_5 (GND), U3.41_6 (GND), U3.41_7 (GND), U3.41_8 (GND), U3.41_9 (GND), U4.2 (VSS), U5.5 (GND), U5.9 (EPAD)
unnamed: D1.1 (K), R9.1
unnamed: J2.A5 (CC1), R15.1
unnamed: J2.B5 (CC2), R13.1
unnamed: J13.3, R16.2
unnamed: Q3.1, R2.2, R14.1
unnamed: R1.1, U1.32 (RCAL0)
unnamed: R1.2, U1.33 (RCAL1)
unnamed: R10.2, U4.5 (PROG)
unnamed: R9.2, U4.1 (STAT)

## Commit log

2026-03-20 Complete HELPStat potentiostat firmware with EIS measurement system
    ESP32-S3 + AD5940 wearable impedance spectroscopy platform supporting USB serial, BLE, SD card, and physical button operation modes. Includes Python data capture scripts, comprehensive documentation,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
    Made-with: Cursor
2026-03-20 Remove stray files (Untitled, deploy_to_github.sh)
    Made-with: Cursor
2026-03-24 Update EIS range to 1Hz-200kHz and apply AD5940 datasheet corrections
    - Set default sweep range to 1 Hz - 200 kHz per paper specification
    - Fix ADC rate double-assignment bug (LP mode now correctly uses 800 kHz)
    - Add ADCBUFCON register switching for HP/LP mode transitions
    - Use ADCPGA_1P5 (production-calibrated) and SINC3 OSR=4 as defaults
    - Fix zero-delay bug in DFT measurement timing calculations
    - Replace flat 1s settling delay with frequency-proportional timing
2026-03-26 Wearable 2-electrode mode, plotting script, docs, USB-safe idle
    - Switch HELPStat switch matrix to 2-electrode (SWP_CE0) across measurement paths
    - main.cpp: wearable auto-sweep timer, WEARABLE/INTERVAL serial commands, remove light sleep on USB-Serial/JTAG (polling wait instead)
    - Add plot_eis_from_file.py for Nyquist/Bode from CSV or Excel
    - README: analysis section, script table, repo layout, wearable timing wording
    Made-with: Cursor
2026-03-30 Reorganize Python tools under testing/; move sample plots; update README
    Made-with: Cursor
2026-03-30 Rename repo references; stop tracking .vscode/settings.json
    Made-with: Cursor
2026-03-31 Add web companion, native iOS app, and Android data visualization
    - web/helpstat-app: PWA-style BLE UI (Web Bluetooth), Pacific-day IndexedDB history, import/export JSON
    - ios/HELPStatCompanion: SwiftUI + CoreBluetooth companion with charts and same JSON history format
    - Android: Data visualization screen, PST day storage, EisPlotHelper, auto-save completed sweeps
    - README: document companions, iOS build/signing, and scenario updates
    Made-with: Cursor
2026-03-31 Fix eis_sweep CSV header match; add scenario1_serial_sample.py for USB capture
    - Recognize firmware line Frequency(Hz) as well as Freq(Hz)
    - Add scenario1_serial_sample.py: Scenario-1 serial sweep with EIS CSV block capture
    Made-with: Cursor
2026-03-31 README: add Troubleshooting (Scenario 3 timing, CSV/scope, QC/filtering)
    Made-with: Cursor
2026-03-31 Set default RCAL to 100 Ohm (on-board nominal); sync docs and scripts
    RCAL value in firmware and MEASURE commands must match the physical
    calibration resistor; brown-black-brown is 100 Ohm, not 1 kOhm.
    Updated main defaults, HELP examples, testing scripts, README, web
    companion placeholder, and MEASUREMENT_MODES examples.
    Made-with: Cursor
2026-03-31 scenario1_serial_sample: send WEARABLE:OFF before MEASURE to avoid queued auto-sweeps when idle
    Made-with: Cursor
2026-03-31 Faster lab sweeps: default WEARABLE off, short scenario1 band, serial sync
    - Default wearableMode false so USB/bench is not blocked by a full auto-sweep; Scenario 3 uses WEARABLE:ON.
    - scenario1_serial_sample: 10 kHz–1 kHz, 2 DFT points, 150 mV; wait for idle before MEASURE; quiet long serial drains.
    - README: document wearable default and field enablement.
    Made-with: Cursor
2026-03-31 Add testing/board_status_wearable.py for STATUS and WEARABLE:ON
    Made-with: Cursor
2026-03-31 board_status_wearable: wait_ready only on Ready line
    Made-with: Cursor
2026-03-31 README: document quick USB scripts, wearable defaults, RCAL, COM troubleshooting
    - Add Quick USB lab scripts section (scenario1_serial_sample, board_status_wearable).
    - List new scripts in repo tree and Python scripts table.
    - Note py -m platformio upload and COM port busy fixes.
    - Expand troubleshooting for PermissionError and sweep blocking serial.
    Made-with: Cursor
2026-03-31 README: expand Scenario 3 with continuous sweep, data paths, persistence
    Made-with: Cursor
2026-03-31 Fix MEASURE:SAMPLE order: handle before generic MEASURE branch (was unreachable)
    Made-with: Cursor
2026-03-31 README: EIS accuracy section (RCAL, RTIA vs RCAL, DFT, SD, LMA, temperature)
    Made-with: Cursor
2026-03-31 Align EIS engine with WatchScript: default 1k RCAL, averaging, sweep fix
    - Default rcalVal/_rcalVal 1000 ohm; document 1k RCAL vs legacy 100 ohm boards
    - runSweep always uses AD5940_DFTMeasureWithAveraging (default _numAverages=3)
    - Fix WithAveraging missing logSweep/configureFrequency (prevent sweep hang)
    - AD5940_DFTMeasure retries validation; stores NaN if all attempts fail
    - README and NEW_FEATURES: WatchScript notes, SD timestamps, testing rcal 1000
    Made-with: Cursor
2026-04-08 Fix DFT poll hang with timeout; CS=38 default; PlatformIO and docs
    - pollDFT returns bool with ~30s timeout; callers handle failure
    - constants.h: CS=38 for current bench wiring; README known issues
    - custom_s3 board JSON, platformio lab-board-cs38 env
    - scenario1_serial_sample waits for System ready
    Made-with: Cursor
2026-04-08 Add KiCad EIS PCB under boards/New_EIS_PCB_Akshay
    - eis_pcb project (schematic + 4-layer PCB), fp/sym tables, fabrication-toolkit options
    - README: document new boards section
    Made-with: Cursor
2026-04-08 Add New_EIS_PCB_Akshay firmware support: SPI DFT polling, display UI, board-specific pins
    Made-with: Cursor
2026-04-08 Rewrite README: concise overview, both board variants, errors/fixes, EIS explanation
    Made-with: Cursor
2026-04-08 Change default RCAL from 1k to 10k Ohm across firmware, scripts, and README
    Made-with: Cursor
2026-04-10 Add display backlight, sweep timings, measurement data, update README
    Made-with: Cursor
2026-04-15 Optimize EIS sweep speed: full 1 Hz-200 kHz in ~108 s (was ~5-6 min)
    Reduce settling delay from 4 to 2 AC periods, cut fixed gain-switch delays from 200 ms to 50 ms, drop per-point averaging from 3 to 1, and lower default points/decade from 10 to 5. All 27 frequency p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
    Made-with: Cursor
2026-04-15 Rename web app to PHEW, update defaults to match firmware
    Rename HELPStat to PHEW across index.html, manifest, app.js, ble.js. Update default sweep parameters: Rct 127k, Rs 150, Rcal 10k, 5 pts/decade, start 200kHz, end 1Hz. Update favicon and PWA icon lett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
    Made-with: Cursor
2026-04-15 Update README with comprehensive PHEW web app documentation
    Add detailed description of the PHEW companion app: what each tab does, data flow diagram, default parameters table, step-by-step access instructions, browser compatibility matrix, and PWA install no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
    Made-with: Cursor
2026-04-15 Add live sweep progress indicator to PHEW web app
    Shows a gradient progress bar, point count (e.g. 5/27), current frequency, and elapsed timer. Updates in real time as each BLE frequency notification arrives. Displays completion summary when sweep f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
    Made-with: Cursor
2026-04-15 Add sweep abort: STOP serial command, BLE stop (start=2), and web app Stop button
    Firmware: volatile _abortSweep flag checked in both runSweep() overloads. Serial STOP command and BLE write of start=2 both trigger abort. Aborted sweeps shut down the AFE cleanly and print partial d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
    Made-with: Cursor
2026-04-15 Update README with sweep abort documentation
    Add STOP to command table, new Stopping a sweep section with all three abort methods, update PHEW instructions to mention Stop button and progress bar, add sweep abort to firmware features list.
    Made-with: Cursor
2026-04-15 Fix BLE sweep trigger: web app can now start sweeps over Bluetooth
    The BLE start characteristic write was never wired into main loop(). Added StartCharCallbacks::onWrite handler for start=1 that sets _bleSweepRequested flag, readBLEParameters() to transfer BLE chara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
    Made-with: Cursor
2026-04-15 Fix BLE sweep defaults: always send all parameters to firmware
    When form fields were left blank (placeholder only), startFreq, endFreq, numPoints, rcalVal, and other params were never sent over BLE, causing the firmware to use stale/uninitialized values. Now all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
    Made-with: Cursor
2026-04-15 Fix BLE transmit order: send data points before Rct/Rs
    BLE_transmitResults() was sending Rct/Rs first, then data points. The web app uses the Rs notification as the sweep-complete signal to finalize and save. Since Rs arrived before any data, finalizeSwe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
    Made-with: Cursor
2026-04-15 Add sweep statistics card to History tab
    Shows fitted parameters (Rct, Rs, Rct+Rs), magnitude range (min, max, mean, span), phase range, and frequency span with point count. Appears between the day/sweep selector and the charts.
    Made-with: Cursor
2026-04-15 Add CSV export for individual sweeps
    Export CSV button in History tab downloads the selected sweep as Frequency,Real,Imaginary,Magnitude,Phase CSV with Rct/Rs appended, matching the firmware serial output format. Filename includes date 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
    Made-with: Cursor
2026-04-15 Document PHEW CSV export in README
    Describe Export CSV in History tab, data flow, backup note, and step-by-step export instructions including filename and column layout.
    Made-with: Cursor
2026-04-15 docs: expand PHEW web app usage and Windows PowerShell notes
    - Document PowerShell 5.x without &&, semicolon/two-line alternatives, py launcher
    - Warn against multiple http.server instances on the same port
    - Clarify hardware/BLE prerequisites, Live/History workflow, export formats
    - Add PHEW troubleshooting table for common browser and connection issues
    Made-with: Cursor
